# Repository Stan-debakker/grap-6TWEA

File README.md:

# GRAP-6TWEA

## Doel
Het doel van dit project was om de verouderde **Elector Proton Robot** te moderniseren.  
Dit heb ik gedaan door het originele PCB (Printed Circuit Board) te vervangen. De nieuwe schema’s zijn te vinden in **"schematics"**.

Daarnaast moest ik ervoor zorgen dat de nieuwe sensoren correct werken.  
Ik ben gestart met experimenteren via Arduino IDE, zie **"code_arduinoIDE"**.

Op basis van deze experimenten heb ik een bibliotheek ontwikkeld om het gebruik te vereenvoudigen:

- **Versie 1** – **"liberary/robot"**: Voor Arduino, met de originele componenten aangesloten.
- **Versie 2** – **"liberary/robot_ESP_addon"**: Voor de ESP32-C6 met de bijbehorende uitbreiding.

## Schoolgerelateerde onderdelen
Omdat dit project deel uitmaakt van een schooltaak, heb ik ook bijbehorende documenten moeten aanmaken, zoals studies en presentaties.  
Deze zijn te vinden onder **"school"**.

Voor een ander vak moest ik een website maken, die grotendeels over dit project gaat. Er staat ook nog extra info over een ander project wat ik vorig jaar deet Asgard.
Je vindt de websitebestanden onder **"website"**.

## Extra experimenten
Tot slot heb ik geëxperimenteerd met communicatie tussen de ESP32 en een computer via Python.  
Door beperkingen op mijn schoollaptop lukte dit niet, en heb ik deze testen stopgezet. De bestanden vind je onder **"python"**.

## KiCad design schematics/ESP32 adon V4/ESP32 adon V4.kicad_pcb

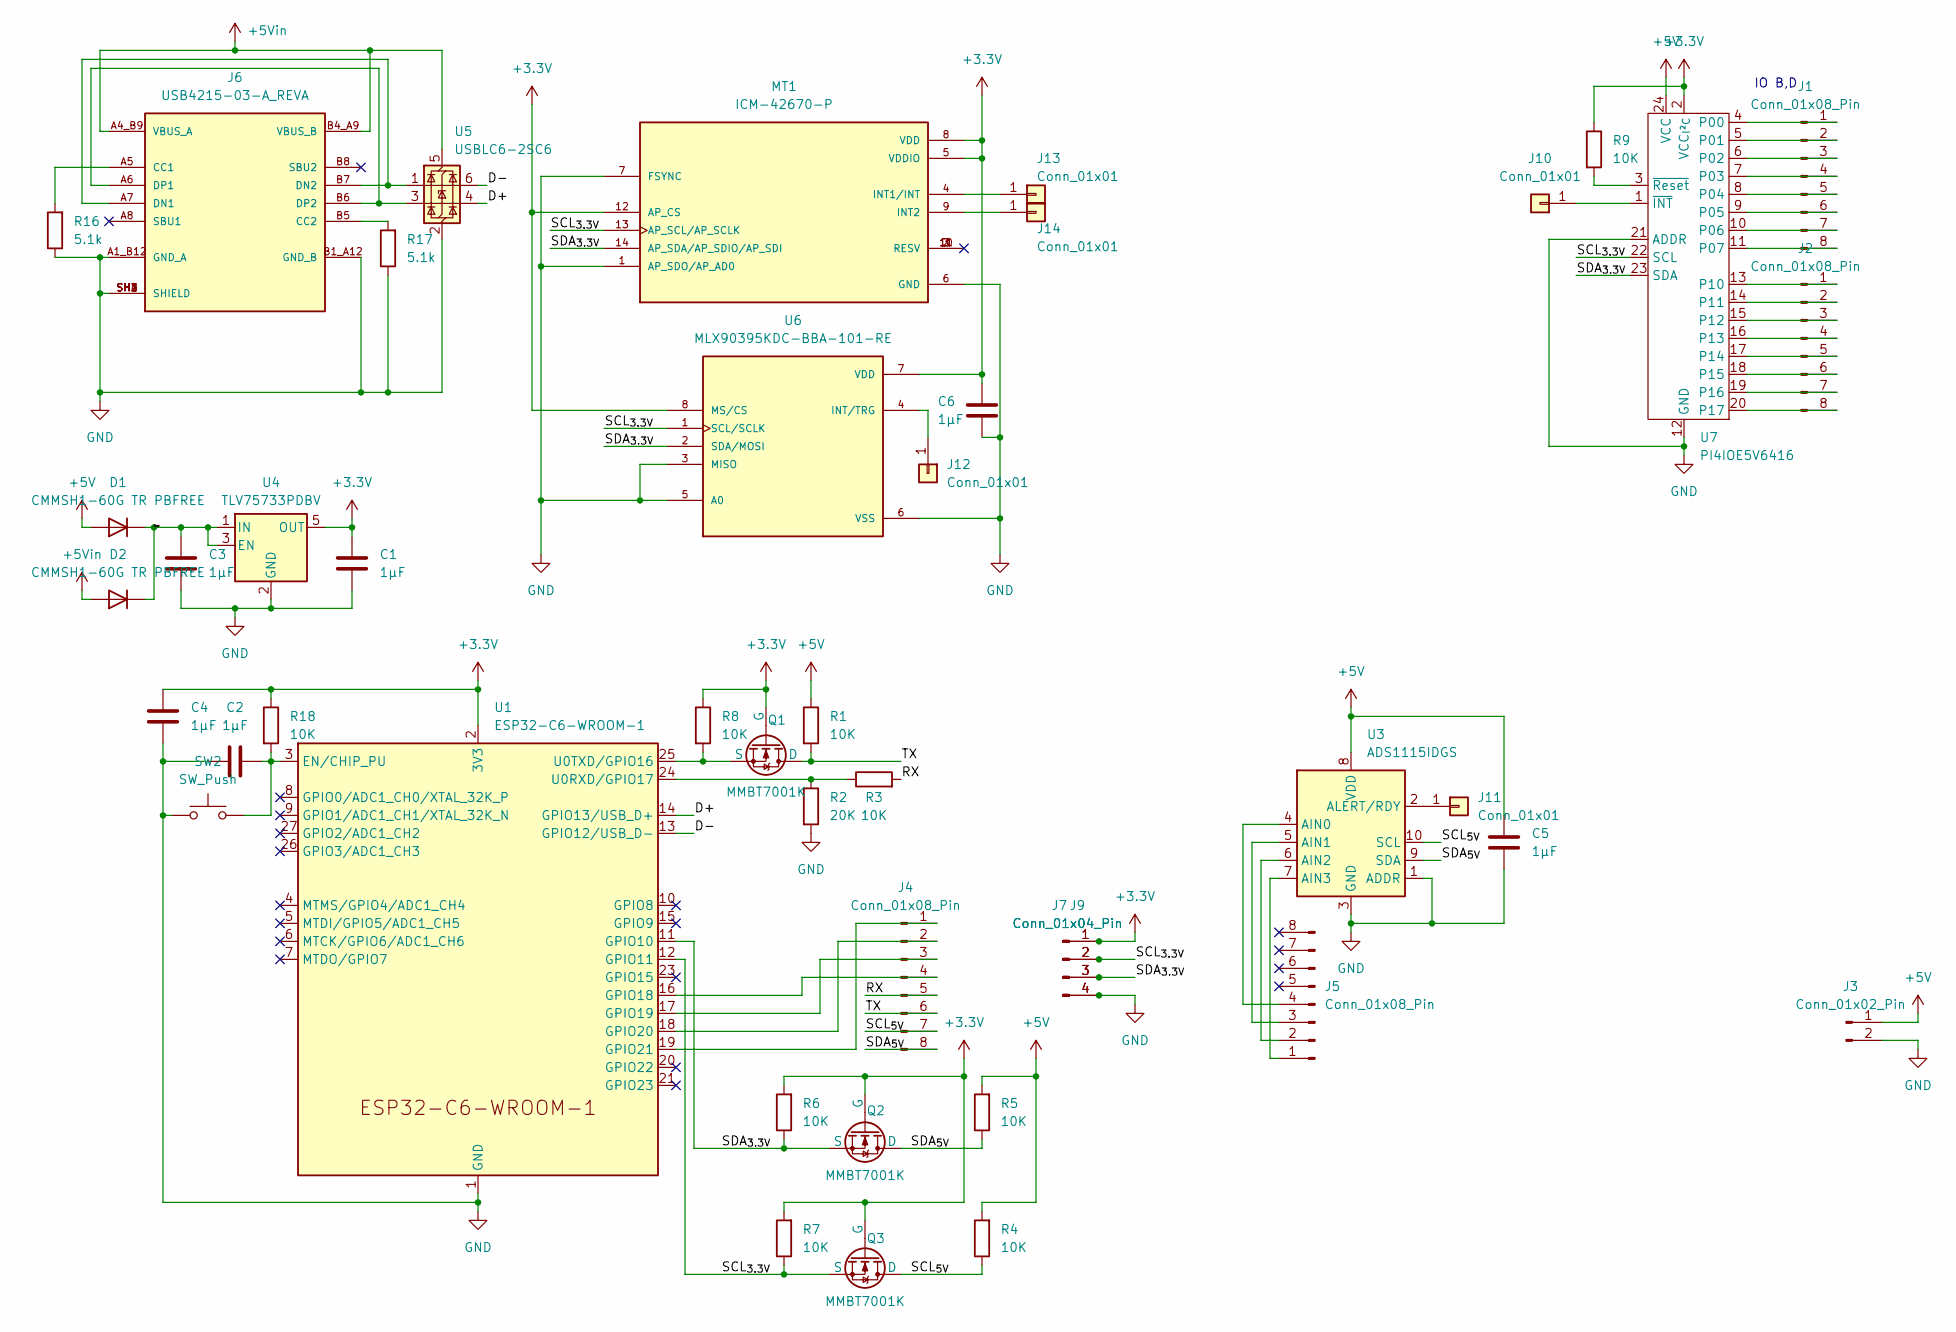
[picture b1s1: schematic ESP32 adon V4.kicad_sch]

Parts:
C1, C2, C3, C4, C5, C6: 1µF; C_0603_1608Metric
D1, D2: CMMSH1-60G TR PBFREE; D_SOD-123F
J1, J2, J4, J5: Conn_01x08_Pin; PinSocket_1x08_P2.54mm_Vertical
J3: Conn_01x02_Pin; PinSocket_1x02_P2.54mm_Vertical
J6: USB4215-03-A_REVA; usb4215-3472997; PARTREV A
J7, J9: Conn_01x04_Pin; PinSocket_1x04_P2.54mm_Vertical
J10, J11, J12, J13, J14: Conn_01x01; SolderWirePad_1x01_SMD_1x2mm
MT1: ICM-42670-P; Bosch_LGA-14_3x2.5mm_P0.5mm; PARTREV 1.1
Q1, Q2, Q3: MMBT7001K; TSOT-23
R1, R3, R4, R5, R6, R7, R8, R9, R18: 10K; R_0603_1608Metric
R2: 20K; R_0603_1608Metric
R16, R17: 5.1k; R_0603_1608Metric
SW2: SW_Push; SW_PUSH_6mm
U1: ESP32-C6-WROOM-1
U3: ADS1115IDGS; TSSOP-10_3x3mm_P0.5mm
U4: TLV75733PDBV; SOT-23-5
U5: USBLC6-2SC6; SOT-23-6
U6: MLX90395KDC-BBA-101-RE; SOIC-8_3.9x4.9mm_P1.27mm; PARTREV 6.0
U7: PI4IOE5V6416; TSSOP-24_4.4x7.8mm_P0.65mm

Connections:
+3.3V: C1.1, C4.2, C6.2, J7.1, J9.1, MT1.5 (VDDIO), MT1.8 (VDD), MT1.12 (AP_CS), Q1.1 (G), Q2.1 (G), Q3.1 (G), R6.2, R7.2, R8.1, R9.1, R18.1, U1.2 (3V3), U4.5 (OUT), U6.7 (VDD), U6.8 (MS/CS), U7.2 (VCC_{I²C})
+5V: C5.2, D1.2 (A), J3.1, R1.1, R4.2, R5.2, U3.8 (VDD), U7.24 (VCC)
+5Vin: D2.2 (A), J6.A4_B9 (VBUS_A), J6.B4_A9 (VBUS_B), U5.5 (VBUS)
/D+: U1.14 (GPIO13/USB_D+), U5.4 (I/O2)
/D-: U1.13 (GPIO12/USB_D-), U5.6 (I/O1)
/RX: J4.5, R3.2
/SCL_{3.3V}: J7.2, J9.2, MT1.13 (AP_SCL/AP_SCLK), Q3.2 (S), R7.1, U1.12 (GPIO11), U6.1 (SCL/SCLK), U7.22 (SCL)
/SCL_{5V}: J4.7, Q3.3 (D), R4.1, U3.10 (SCL)
/SDA_{3.3V}: J7.3, J9.3, MT1.14 (AP_SDA/AP_SDIO/AP_SDI), Q2.2 (S), R6.1, U1.11 (GPIO10), U6.2 (SDA/MOSI), U7.23 (SDA)
/SDA_{5V}: J4.8, Q2.3 (D), R5.1, U3.9 (SDA)
/TX: J4.6, Q1.3 (D), R1.2
/Vin_reg: C3.1, D1.1 (K), D2.1 (K), U4.1 (IN), U4.3 (EN)
GND: C1.2, C2.1, C3.2, C4.1, C5.1, C6.1, J3.2, J6.A1_B12 (GND_A), J6.B1_A12 (GND_B), J6.SH1 (SHIELD), J6.SH2 (SHIELD), J6.SH3 (SHIELD), J6.SH4 (SHIELD), J7.4, J9.4, MT1.1 (AP_SDO/AP_AD0), MT1.6 (GND), MT1.7 (FSYNC), R2.2, R16.1, R17.1, SW2.1, U1.1 (GND), U1.28 (GND), U1.29 (GND), U3.1 (ADDR), U3.3 (GND), U4.2 (GND), U5.2 (GND), U6.3 (MISO), U6.5 (A0), U6.6 (VSS), U7.12 (GND), U7.21 (ADDR)
unnamed: J1.1, U7.4 (P00)
unnamed: J1.2, U7.5 (P01)
unnamed: J1.3, U7.6 (P02)
unnamed: J1.4, U7.7 (P03)
unnamed: J1.5, U7.8 (P04)
unnamed: J1.6, U7.9 (P05)
unnamed: J1.7, U7.10 (P06)
unnamed: J1.8, U7.11 (P07)
unnamed: J2.1, U7.13 (P10)
unnamed: J2.2, U7.14 (P11)
unnamed: J2.3, U7.15 (P12)
unnamed: J2.4, U7.16 (P13)
unnamed: J2.5, U7.17 (P14)
unnamed: J2.6, U7.18 (P15)
unnamed: J2.7, U7.19 (P16)
unnamed: J2.8, U7.20 (P17)
unnamed: J4.1, U1.19 (GPIO21)
unnamed: J4.2, U1.18 (GPIO20)
unnamed: J4.3, U1.17 (GPIO19)
unnamed: J4.4, U1.16 (GPIO18)
unnamed: J5.1, U3.7 (AIN3)
unnamed: J5.2, U3.6 (AIN2)
unnamed: J5.3, U3.5 (AIN1)
unnamed: J5.4, U3.4 (AIN0)
unnamed: J6.A5 (CC1), R16.2
unnamed: J6.B5 (CC2), R17.2
unnamed: J6.A7 (DN1), J6.B7 (DN2), U5.1 (I/O1)
unnamed: J6.A6 (DP1), J6.B6 (DP2), U5.3 (I/O2)
unnamed: J10.1, U7.1 (~INT)
unnamed: J11.1, U3.2 (ALERT/RDY)
unnamed: J12.1, U6.4 (INT/TRG)
unnamed: J13.1, MT1.4 (INT1/INT)
unnamed: J14.1, MT1.9 (INT2)
unnamed: Q1.2 (S), R8.2, U1.25 (U0TXD/GPIO16)
unnamed: C2.2, R18.2, SW2.2, U1.3 (EN/CHIP_PU)
unnamed: R2.1, R3.1, U1.24 (U0RXD/GPIO17)
unnamed: R9.2, U7.3 (~Reset)

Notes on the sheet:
IO B,D

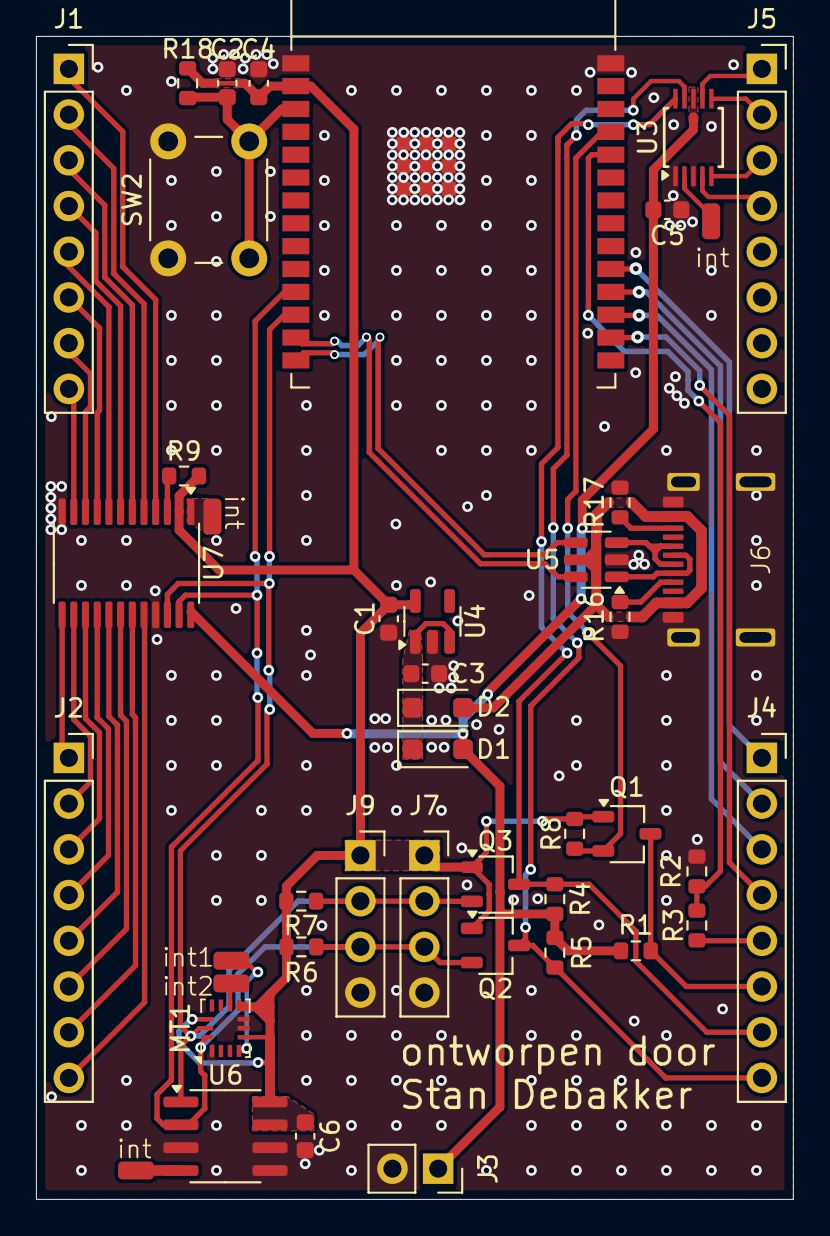
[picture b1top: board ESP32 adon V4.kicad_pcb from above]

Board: 2 copper layers, 42.0 x 64.6 mm, 44 parts (0 on the bottom side), 50 nets.

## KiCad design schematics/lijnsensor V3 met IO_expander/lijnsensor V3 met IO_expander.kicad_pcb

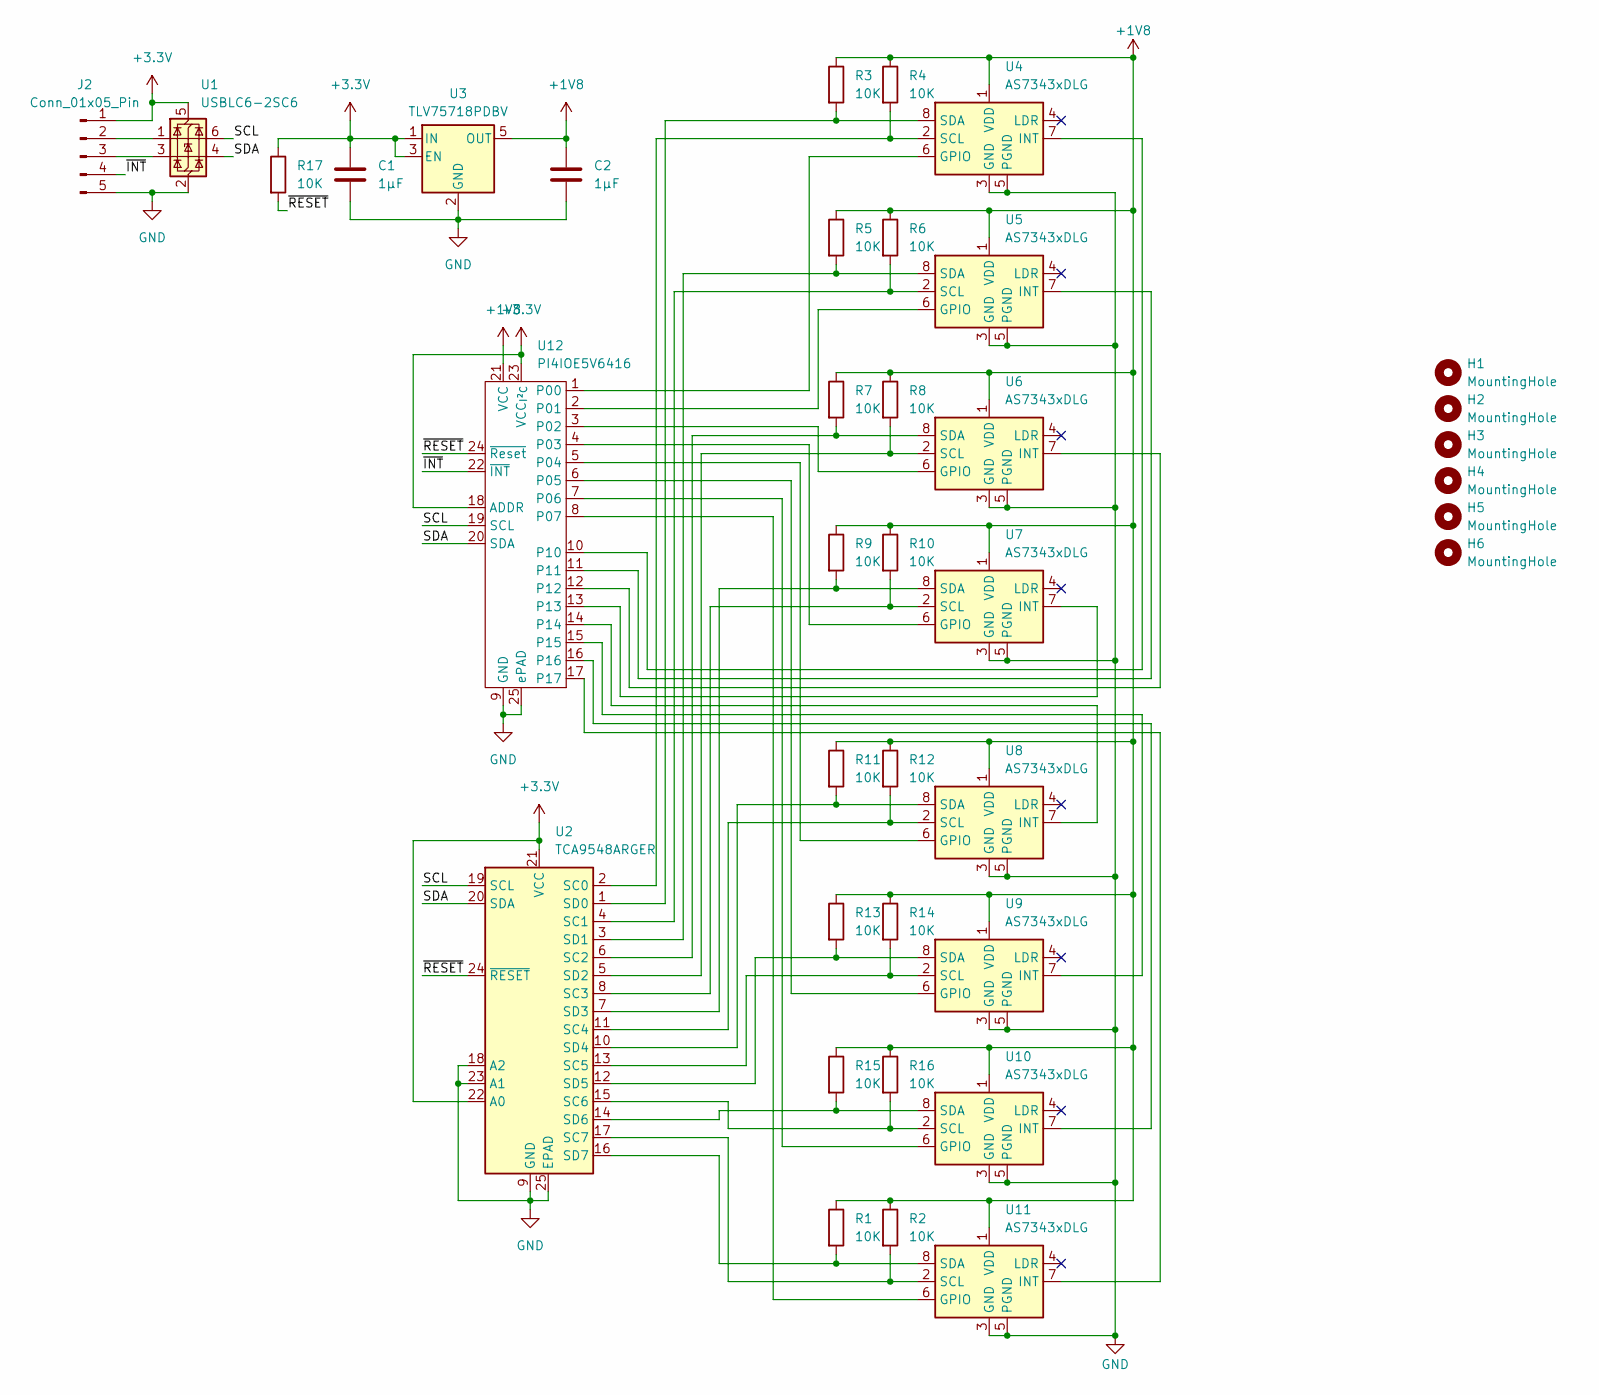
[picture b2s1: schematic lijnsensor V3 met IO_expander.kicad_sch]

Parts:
C1, C2: 1µF; C_0603_1608Metric
H1, H2, H3, H4: MountingHole; MountingHole_4.3mm_M4
H5, H6: MountingHole; MountingHole_8.4mm_M8
J2: Conn_01x05_Pin; PinHeader_1x05_P2.54mm_Vertical
R1, R2, R3, R4, R5, R6, R7, R8, R9, R10, R11, R12, R13, R14, R15, R16, R17: 10K; R_0603_1608Metric
U1: USBLC6-2SC6; SOT-23-6
U2: TCA9548ARGER; Texas_RGE0024H_VQFN-24-1EP_4x4mm_P0.5mm_EP2.7x2.7mm
U3: TLV75718PDBV; SOT-23-5
U4, U5, U6, U7, U8, U9, U10, U11: AS7343xDLG; AMS_OLGA-8_2x3.1mm_P0.8mm
U12: PI4IOE5V6416

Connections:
+1V8: C2.1, R1.1, R2.1, R3.1, R4.1, R5.1, R6.1, R7.1, R8.1, R9.1, R10.1, R11.1, R12.1, R13.1, R14.1, R15.1, R16.1, U3.5 (OUT), U4.1 (VDD), U5.1 (VDD), U6.1 (VDD), U7.1 (VDD), U8.1 (VDD), U9.1 (VDD), U10.1 (VDD), U11.1 (VDD), U12.21 (VCC)
+3.3V: C1.1, J2.1, R17.1, U1.5 (VBUS), U2.21 (VCC), U2.22 (A0), U3.1 (IN), U3.3 (EN), U12.18 (ADDR), U12.23 (VCC_{I²C})
/SCL: U1.6 (I/O1), U2.19 (SCL), U12.19 (SCL)
/SDA: U1.4 (I/O2), U2.20 (SDA), U12.20 (SDA)
/~INT: J2.4, U12.22 (~INT)
/~RESET: R17.2, U2.24 (~RESET), U12.24 (~Reset)
GND: C1.2, C2.2, J2.5, U1.2 (GND), U2.9 (GND), U2.18 (A2), U2.23 (A1), U2.25 (EPAD), U3.2 (GND), U4.3 (GND), U4.5 (PGND), U5.3 (GND), U5.5 (PGND), U6.3 (GND), U6.5 (PGND), U7.3 (GND), U7.5 (PGND), U8.3 (GND), U8.5 (PGND), U9.3 (GND), U9.5 (PGND), U10.3 (GND), U10.5 (PGND), U11.3 (GND), U11.5 (PGND), U12.9 (GND), U12.25 (ePAD)
unnamed: J2.2, U1.1 (I/O1)
unnamed: J2.3, U1.3 (I/O2)
unnamed: R4.2, U2.2 (SC0), U4.2 (SCL)
unnamed: R6.2, U2.4 (SC1), U5.2 (SCL)
unnamed: R7.2, U2.6 (SC2), U6.8 (SDA)
unnamed: R10.2, U2.8 (SC3), U7.2 (SCL)
unnamed: R12.2, U2.11 (SC4), U8.2 (SCL)
unnamed: R14.2, U2.13 (SC5), U9.2 (SCL)
unnamed: R3.2, U2.1 (SD0), U4.8 (SDA)
unnamed: R5.2, U2.3 (SD1), U5.8 (SDA)
unnamed: R8.2, U2.5 (SD2), U6.2 (SCL)
unnamed: R9.2, U2.7 (SD3), U7.8 (SDA)
unnamed: R11.2, U2.10 (SD4), U8.8 (SDA)
unnamed: R13.2, U2.12 (SD5), U9.8 (SDA)
unnamed: U10.6 (GPIO), U12.7 (P06)
unnamed: U10.7 (INT), U12.16
unnamed: R16.2, U2.15 (SC6), U10.2 (SCL)
unnamed: R15.2, U2.14 (SD6), U10.8 (SDA)
unnamed: U11.6 (GPIO), U12.8 (P07)
unnamed: U11.7 (INT), U12.17
unnamed: R2.2, U2.17 (SC7), U11.2 (SCL)
unnamed: R1.2, U2.16 (SD7), U11.8 (SDA)
unnamed: U4.6 (GPIO), U12.1 (P00)
unnamed: U5.6 (GPIO), U12.2 (P01)
unnamed: U6.6 (GPIO), U12.3 (P02)
unnamed: U7.6 (GPIO), U12.4 (P03)
unnamed: U8.6 (GPIO), U12.5 (P04)
unnamed: U9.6 (GPIO), U12.6 (P05)
unnamed: U4.7 (INT), U12.10
unnamed: U5.7 (INT), U12.11
unnamed: U6.7 (INT), U12.12
unnamed: U7.7 (INT), U12.13
unnamed: U8.7 (INT), U12.14
unnamed: U9.7 (INT), U12.15

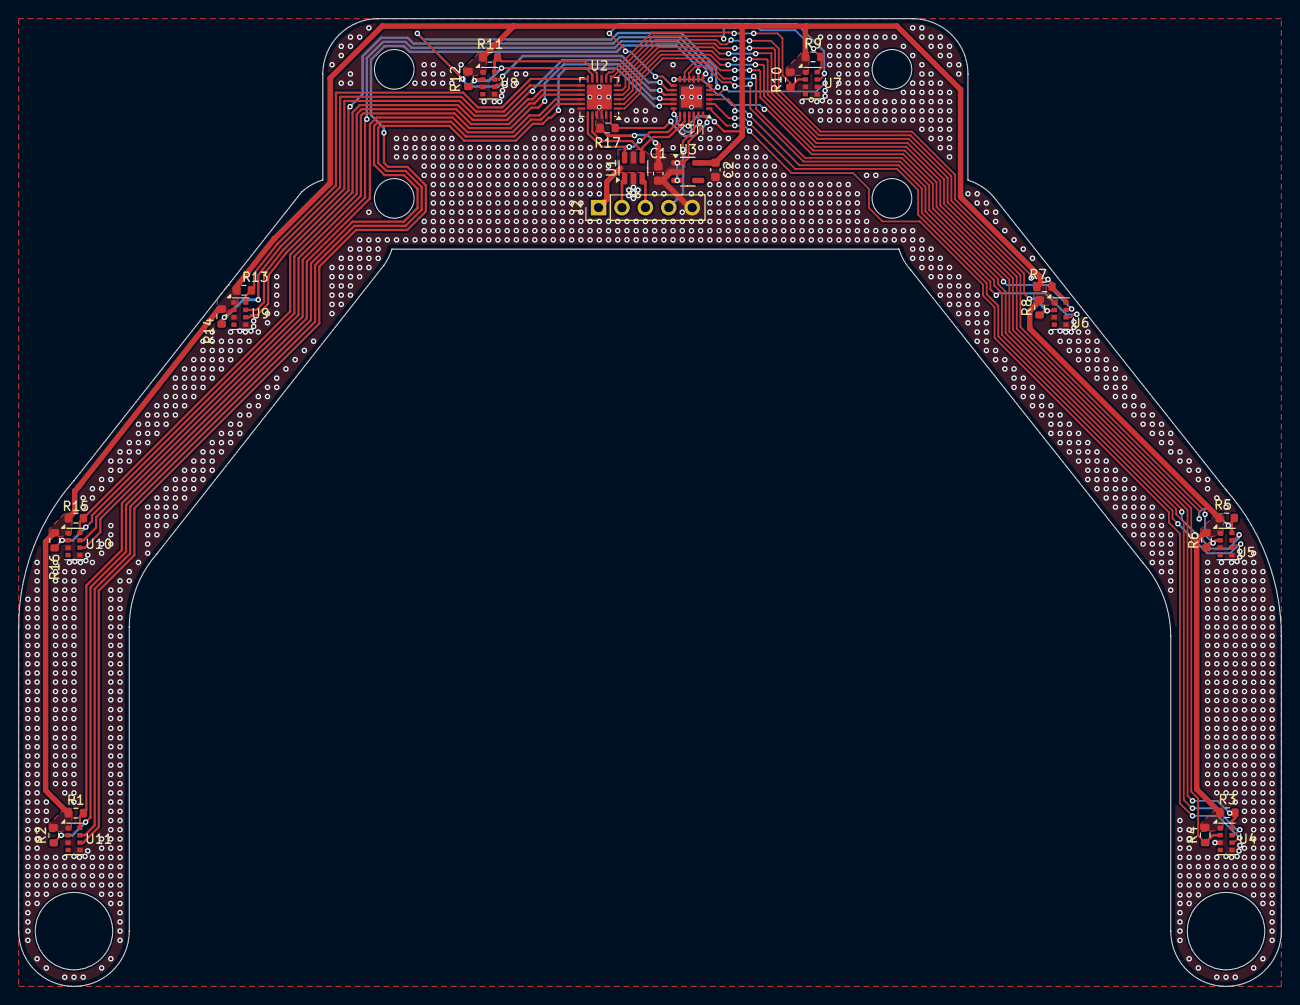
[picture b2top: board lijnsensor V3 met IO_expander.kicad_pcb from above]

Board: 2 copper layers, 137.0 x 105.0 mm, 38 parts (0 on the bottom side), 41 nets.

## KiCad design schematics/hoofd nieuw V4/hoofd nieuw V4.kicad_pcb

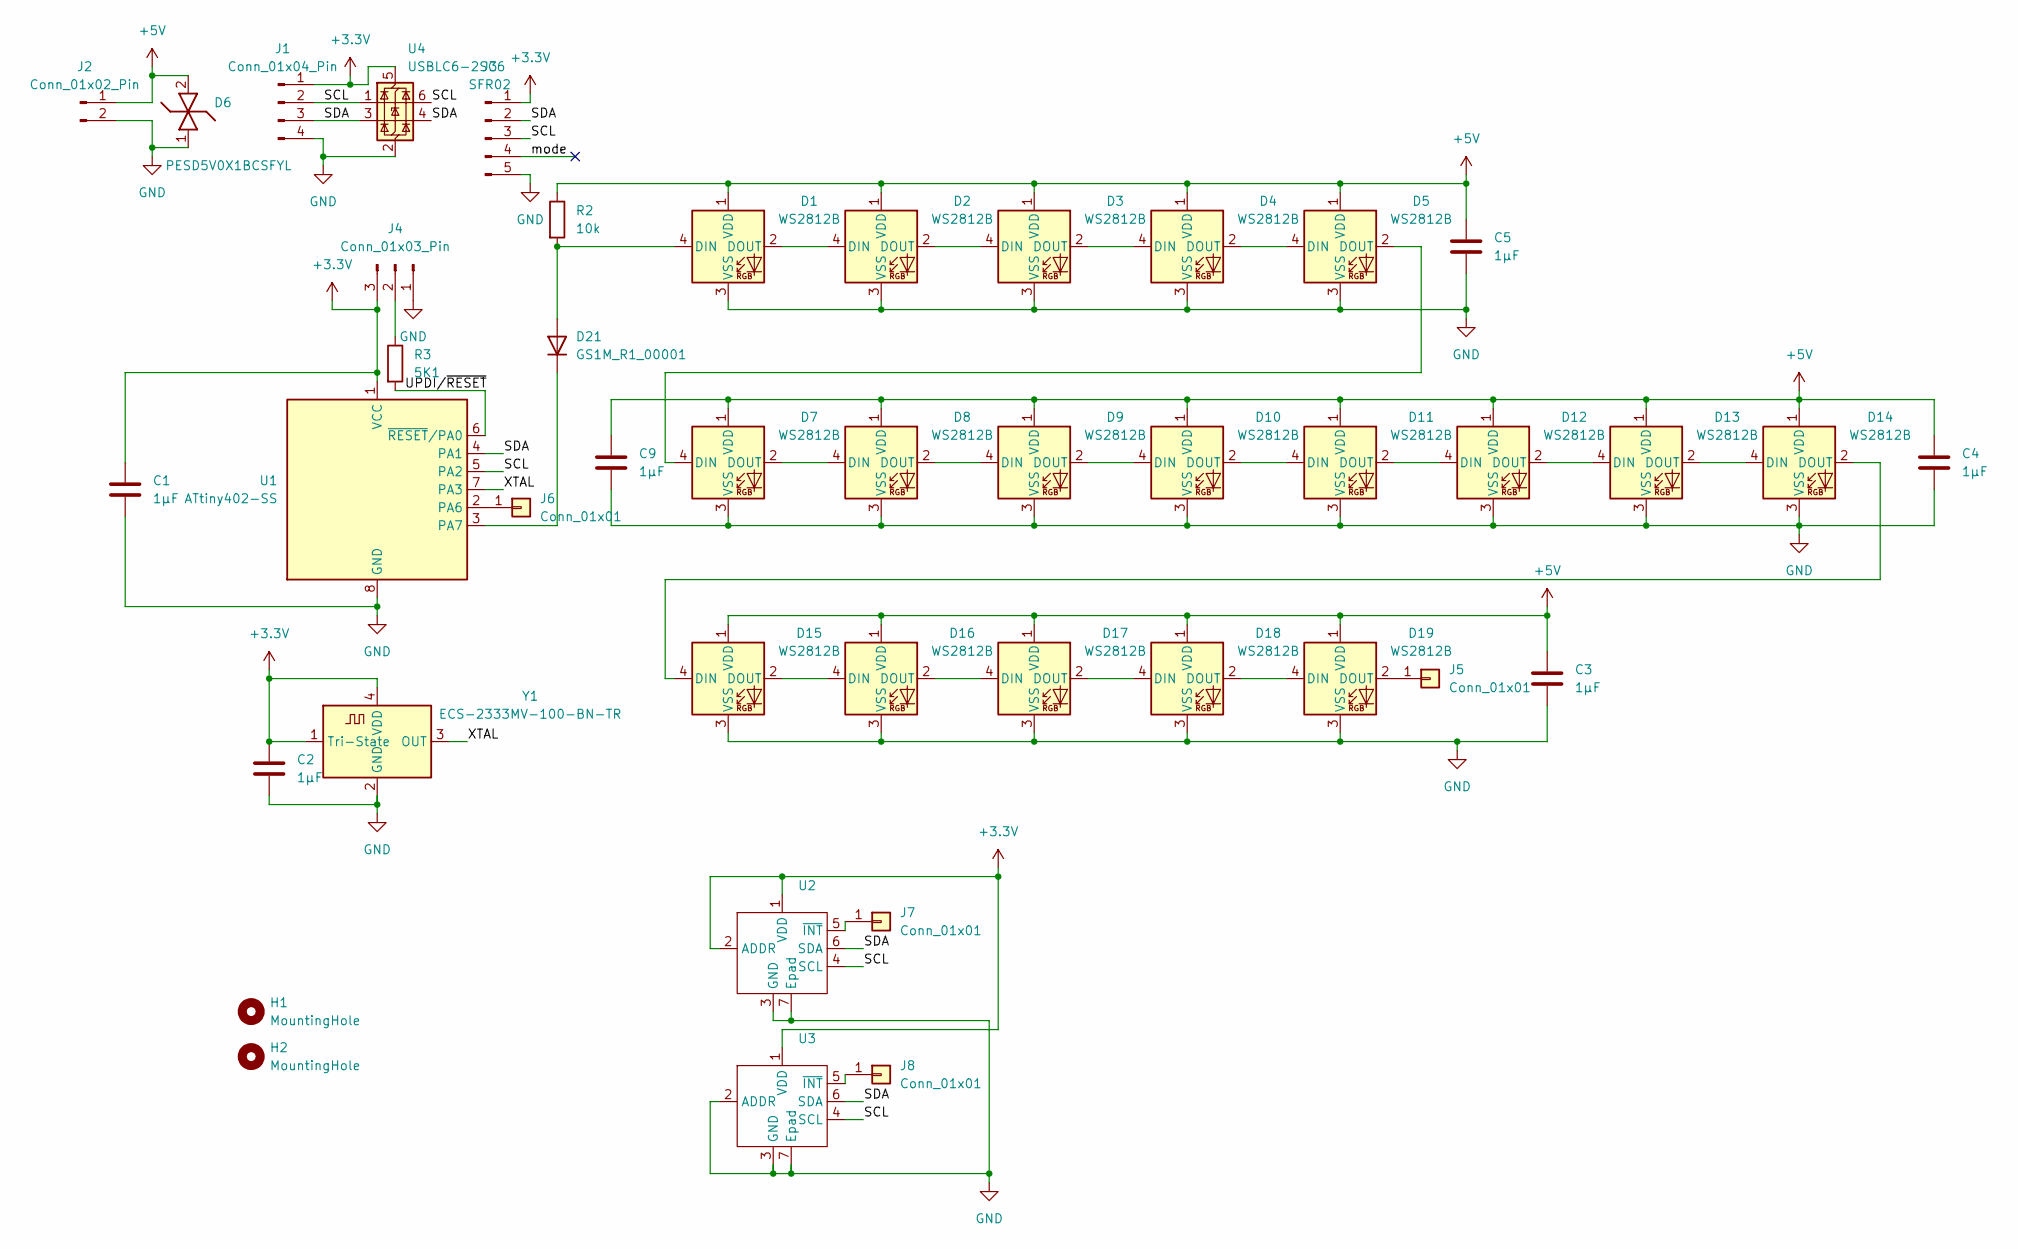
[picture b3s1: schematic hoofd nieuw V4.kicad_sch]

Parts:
C1, C2, C3, C4, C5, C9: 1µF; C_0603_1608Metric
D1, D2, D3, D4, D5, D7, D8, D9, D10, D11, D12, D13, D14, D15, D16, D17, D18, D19: WS2812B; LED_WS2812B_PLCC4_5.0x5.0mm_P3.2mm
D6: PESD5V0X1BCSFYL; PMEG3005AESFYL; Mouser Part Number 771-PESD5V0X1BCSFYL
D21: GS1M_R1_00001; D_SMA
H1, H2: MountingHole; MountingHole_3.5mm
J1: Conn_01x04_Pin; PinHeader_1x04_P2.54mm_Vertical
J2: Conn_01x02_Pin; PinHeader_1x02_P2.54mm_Vertical
J3: SFR02; PinHeader_1x05_P2.54mm_Vertical
J4: Conn_01x03_Pin; PinHeader_1x03_P2.54mm_Vertical
J5, J6, J7, J8: Conn_01x01; SolderWirePad_1x01_SMD_1x2mm
R2: 10k; R_0603_1608Metric
R3: 5K1; R_0603_1608Metric
U1: ATtiny402-SS; SOIC-8_3.9x4.9mm_P1.27mm
U2, U3: Texas_PWSON-N6
U4: USBLC6-2SC6; SOT-23-6
Y1: ECS-2333MV-100-BN-TR; ESC-2333-xxx-xxx

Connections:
+3.3V: C1.1, C2.1, J1.1, J3.1, J4.3, U1.1 (VCC), U2.1 (VDD), U2.2 (ADDR), U3.1 (VDD), U4.5 (VBUS), Y1.1 (Tri-State), Y1.4 (VDD)
+5V: C3.1, C4.1, C5.1, C9.1, D1.1 (VDD), D2.1 (VDD), D3.1 (VDD), D4.1 (VDD), D5.1 (VDD), D6.2 (K2), D7.1 (VDD), D8.1 (VDD), D9.1 (VDD), D10.1 (VDD), D11.1 (VDD), D12.1 (VDD), D13.1 (VDD), D14.1 (VDD), D15.1 (VDD), D16.1 (VDD), D17.1 (VDD), D18.1 (VDD), D19.1 (VDD), J2.1, R2.1
/SCL: J1.2, J3.3, U1.5 (PA2), U2.4 (SCL), U3.4 (SCL), U4.1 (I/O1), U4.6 (I/O1)
/SDA: J1.3, J3.2, U1.4 (PA1), U2.6 (SDA), U3.6 (SDA), U4.3 (I/O2), U4.4 (I/O2)
/UPDI/~RESET: R3.2, U1.6 (~RESET/PA0)
/XTAL: U1.7 (PA3), Y1.3 (OUT)
/mode: J3.4
GND: C1.2, C2.2, C3.2, C4.2, C5.2, C9.2, D1.3 (VSS), D2.3 (VSS), D3.3 (VSS), D4.3 (VSS), D5.3 (VSS), D6.1 (K1), D7.3 (VSS), D8.3 (VSS), D9.3 (VSS), D10.3 (VSS), D11.3 (VSS), D12.3 (VSS), D13.3 (VSS), D14.3 (VSS), D15.3 (VSS), D16.3 (VSS), D17.3 (VSS), D18.3 (VSS), D19.3 (VSS), J1.4, J2.2, J3.5, J4.1, U1.8 (GND), U2.3 (GND), U2.7 (Epad), U3.2 (ADDR), U3.3 (GND), U3.7 (Epad), U4.2 (GND), Y1.2 (GND)
unnamed: D1.4 (DIN), D21.2 (A), R2.2
unnamed: D1.2 (DOUT), D2.4 (DIN)
unnamed: D2.2 (DOUT), D3.4 (DIN)
unnamed: D3.2 (DOUT), D4.4 (DIN)
unnamed: D4.2 (DOUT), D5.4 (DIN)
unnamed: D5.2 (DOUT), D7.4 (DIN)
unnamed: D7.2 (DOUT), D8.4 (DIN)
unnamed: D8.2 (DOUT), D9.4 (DIN)
unnamed: D9.2 (DOUT), D10.4 (DIN)
unnamed: D10.2 (DOUT), D11.4 (DIN)
unnamed: D11.2 (DOUT), D12.4 (DIN)
unnamed: D12.2 (DOUT), D13.4 (DIN)
unnamed: D13.2 (DOUT), D14.4 (DIN)
unnamed: D14.2 (DOUT), D15.4 (DIN)
unnamed: D15.2 (DOUT), D16.4 (DIN)
unnamed: D16.2 (DOUT), D17.4 (DIN)
unnamed: D17.2 (DOUT), D18.4 (DIN)
unnamed: D18.2 (DOUT), D19.4 (DIN)
unnamed: D19.2 (DOUT), J5.1
unnamed: D21.1 (K), U1.3 (PA7)
unnamed: J4.2, R3.1
unnamed: J6.1, U1.2 (PA6)
unnamed: J7.1, U2.5 (~INT)
unnamed: J8.1, U3.5 (~INT)

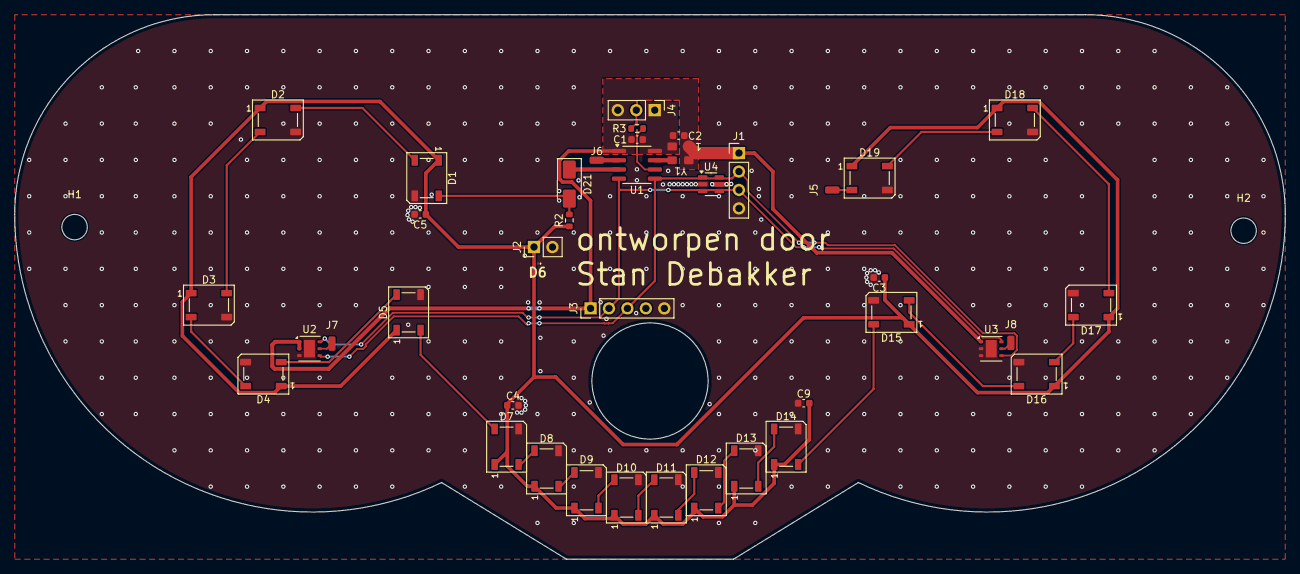
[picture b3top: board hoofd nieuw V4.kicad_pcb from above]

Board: 2 copper layers, 175.0 x 75.0 mm, 43 parts (0 on the bottom side), 31 nets.

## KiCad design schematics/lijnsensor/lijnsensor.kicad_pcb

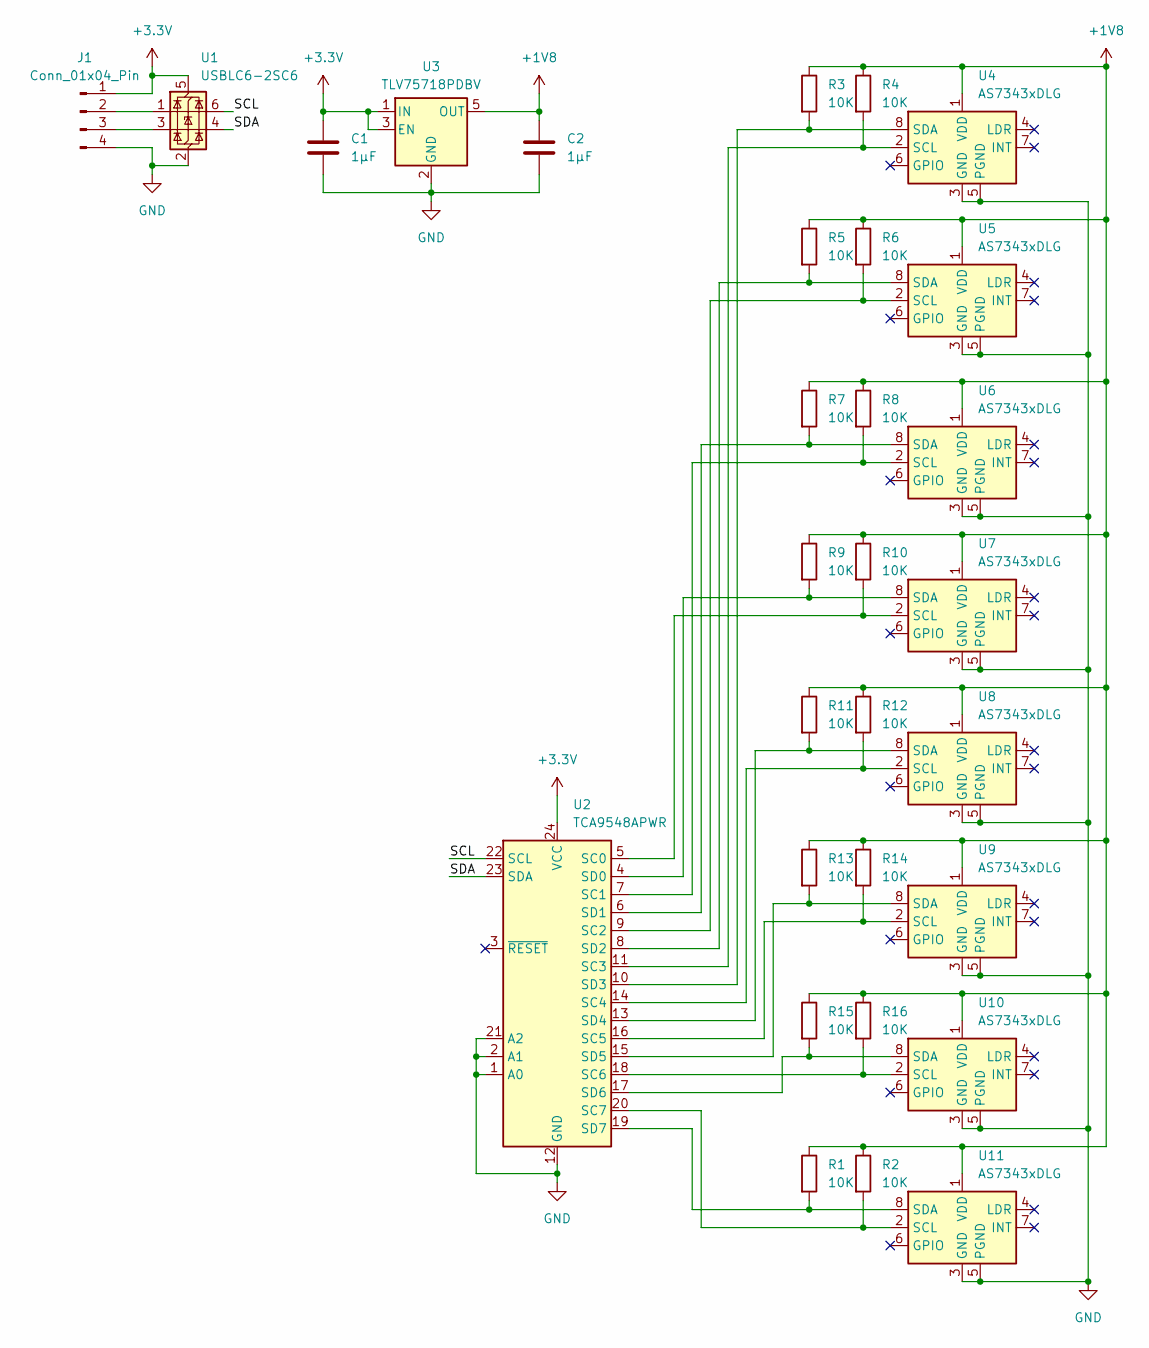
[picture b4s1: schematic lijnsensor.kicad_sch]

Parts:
C1, C2: 1µF; C_0603_1608Metric
J1: Conn_01x04_Pin; PinHeader_1x04_P2.54mm_Vertical
R1, R2, R3, R4, R5, R6, R7, R8, R9, R10, R11, R12, R13, R14, R15, R16: 10K; R_0603_1608Metric
U1: USBLC6-2SC6; SOT-23-6
U2: TCA9548APWR; TSSOP-24_4.4x7.8mm_P0.65mm
U3: TLV75718PDBV; SOT-23-5
U4, U5, U6, U7, U8, U9, U10, U11: AS7343xDLG; AMS_OLGA-8_2x3.1mm_P0.8mm

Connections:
+1V8: C2.1, R1.1, R2.1, R3.1, R4.1, R5.1, R6.1, R7.1, R8.1, R9.1, R10.1, R11.1, R12.1, R13.1, R14.1, R15.1, R16.1, U3.5 (OUT), U4.1 (VDD), U5.1 (VDD), U6.1 (VDD), U7.1 (VDD), U8.1 (VDD), U9.1 (VDD), U10.1 (VDD), U11.1 (VDD)
+3.3V: C1.1, J1.1, U1.5 (VBUS), U2.24 (VCC), U3.1 (IN), U3.3 (EN)
/SCL: U1.6 (I/O1), U2.22 (SCL)
/SDA: U1.4 (I/O2), U2.23 (SDA)
GND: C1.2, C2.2, J1.4, U1.2 (GND), U2.1 (A0), U2.2 (A1), U2.12 (GND), U2.21 (A2), U3.2 (GND), U4.3 (GND), U4.5 (PGND), U5.3 (GND), U5.5 (PGND), U6.3 (GND), U6.5 (PGND), U7.3 (GND), U7.5 (PGND), U8.3 (GND), U8.5 (PGND), U9.3 (GND), U9.5 (PGND), U10.3 (GND), U10.5 (PGND), U11.3 (GND), U11.5 (PGND)
unnamed: J1.2, U1.1 (I/O1)
unnamed: J1.3, U1.3 (I/O2)
unnamed: R10.2, U2.5 (SC0), U7.2 (SCL)
unnamed: R8.2, U2.7 (SC1), U6.2 (SCL)
unnamed: R6.2, U2.9 (SC2), U5.2 (SCL)
unnamed: R4.2, U2.11 (SC3), U4.2 (SCL)
unnamed: R12.2, U2.14 (SC4), U8.2 (SCL)
unnamed: R14.2, U2.16 (SC5), U9.2 (SCL)
unnamed: R9.2, U2.4 (SD0), U7.8 (SDA)
unnamed: R7.2, U2.6 (SD1), U6.8 (SDA)
unnamed: R5.2, U2.8 (SD2), U5.8 (SDA)
unnamed: R3.2, U2.10 (SD3), U4.8 (SDA)
unnamed: R11.2, U2.13 (SD4), U8.8 (SDA)
unnamed: R13.2, U2.15 (SD5), U9.8 (SDA)
unnamed: R16.2, U2.18 (SC6), U10.2 (SCL)
unnamed: R15.2, U2.17 (SD6), U10.8 (SDA)
unnamed: R2.2, U2.20 (SC7), U11.2 (SCL)
unnamed: R1.2, U2.19 (SD7), U11.8 (SDA)

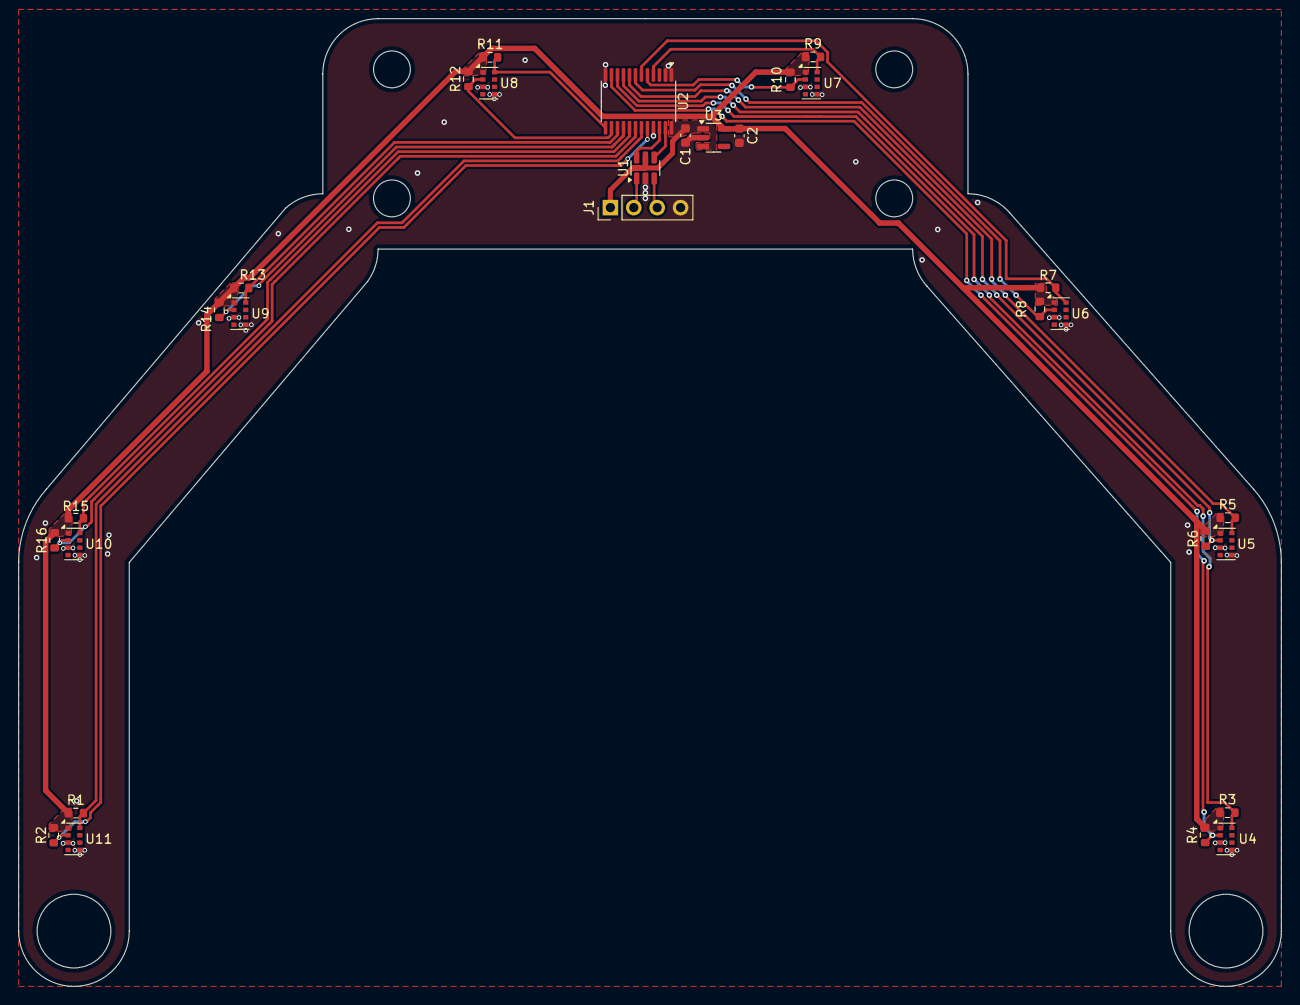
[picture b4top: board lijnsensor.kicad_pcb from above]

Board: 2 copper layers, 137.0 x 105.0 mm, 30 parts (0 on the bottom side), 23 nets.
